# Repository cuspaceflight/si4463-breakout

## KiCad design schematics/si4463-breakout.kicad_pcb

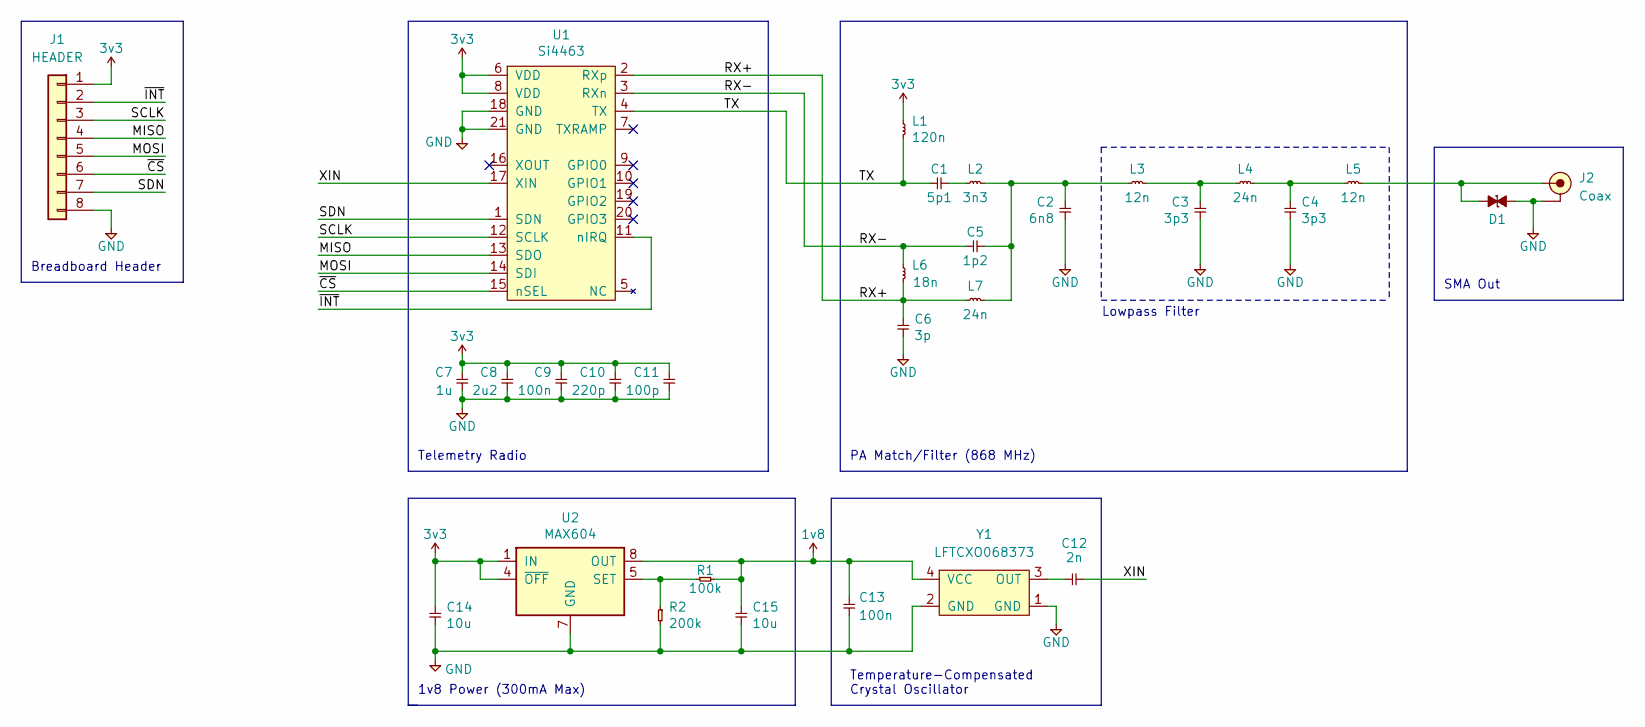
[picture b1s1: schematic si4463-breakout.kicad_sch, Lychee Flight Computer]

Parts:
C1: 5p1; C_0402; Farnell 2781439
C2: 6n8; C_0402; Farnell 2627370
C3, C4: 3p3; C_0402; Farnell 3013357
C5: 1p2; C_0402; Farnell 3369062
C6: 3p; C_0402; Farnell 1758933
C7: 1u; C_0402; Farnell 9402063
C8: 2u2; C_0402; Farnell 2672111
C9, C13: 100n; C_0402; Farnell 9402047
C10: 220p; C_0402; Farnell 3019240
C11: 100p; C_0402; Farnell 2906905
C12: 2n; C_0402; Farnell 2332520
C14, C15: 10u; C_0402; Farnell 3369188
D1: D_ESD; D_0402; Farnell 2368169
J1: HEADER; Header_Breadboard_1x08; Farnell 1022256
J2: Coax; SMA-Edge; Farnell 1608592
L1: 120n; L_0402; Farnell 3471254
L2: 3n3; L_0402; Farnell 1343068
L3, L5: 12n; L_0402; Farnell 1343082
L4, L7: 24n; L_0402; Farnell 3263549
L6: 18n; L_0402; Farnell 1343084
R1: 100k; R_0402; Farnell 2447094
R2: 200k; R_0402; Farnell 2059185
U1: Si4463; Farnell 2462637
U2: MAX604; Farnell 2799174
Y1: LFTCXO068373; Farnell 2627327

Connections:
1v8: C13.1, C15.1, R1.2, U2.8 (OUT), Y1.4 (VCC)
3v3: C7.1, C8.1, C9.1, C10.1, C11.1, C14.1, J1.1, L1.1, U1.6 (VDD), U1.8 (VDD), U2.1 (IN), U2.4 (~OFF)
/MISO: J1.4, U1.13 (SDO)
/MOSI: J1.5, U1.14 (SDI)
/RX+: C6.1, L6.2, L7.1, U1.2 (RXp)
/RX-: C5.1, L6.1, U1.3 (RXn)
/SCLK: J1.3, U1.12 (SCLK)
/SDN: J1.7, U1.1 (SDN)
/TX: C1.1, L1.2, U1.4 (TX)
/XIN: C12.2, U1.17 (XIN)
/~CS: J1.6, U1.15 (nSEL)
/~INT: J1.2, U1.11 (nIRQ)
GND: C2.2, C3.2, C4.2, C6.2, C7.2, C8.2, C9.2, C10.2, C11.2, C13.2, C14.2, C15.2, D1.2, J1.8, J2.2 (GND), R2.2, U1.18 (GND), U1.21 (GND), U2.2 (GND), U2.3 (GND), U2.6 (GND), U2.7 (GND), Y1.1 (GND), Y1.2 (GND)
unnamed: C1.2, L2.1
unnamed: C2.1, C5.2, L2.2, L3.1, L7.2
unnamed: C3.1, L3.2, L4.1
unnamed: C4.1, L4.2, L5.1
unnamed: C12.1, Y1.3 (OUT)
unnamed: D1.1, J2.1 (RF), L5.2
unnamed: R1.1, R2.1, U2.5 (SET)

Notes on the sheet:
PA Match/Filter (868 MHz)
Lowpass Filter
1v8 Power (300mA Max)
Telemetry Radio
Temperature-Compensated Crystal Oscillator
SMA Out
Breadboard Header

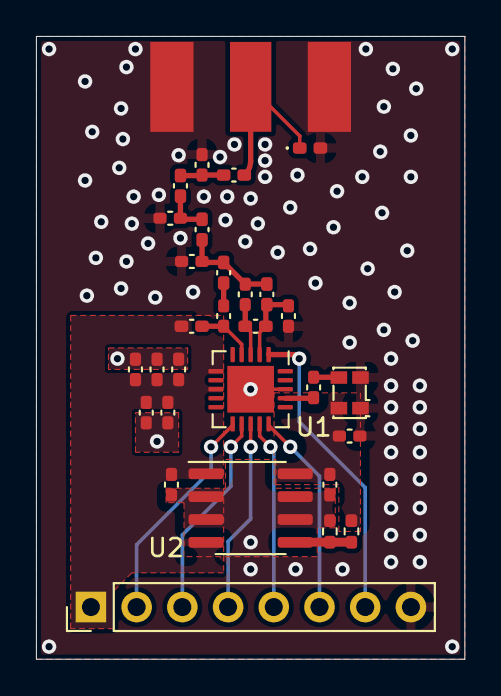
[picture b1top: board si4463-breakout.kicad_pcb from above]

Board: 2 copper layers, 23.8 x 34.6 mm, 30 parts (0 on the bottom side), 20 nets.

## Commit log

2022-01-27 Fix library references
2022-01-27 Update submodule
